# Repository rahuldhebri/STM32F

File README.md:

# STM32F4
* STM32F4 microcontroller board with 10 GPIO pins with terminal connectors, SWD, I2C, USART & USB for DFU.
* Designed in KiCAD all source and manufacturing files included.
* Assembly and Gerber files are in format which JLCPCB uses and all parts used are basic parts so additional cost is not charged for using extended parts.
* Feel free to make any changes and use for your project and also mention suggestions/improvements/issues.

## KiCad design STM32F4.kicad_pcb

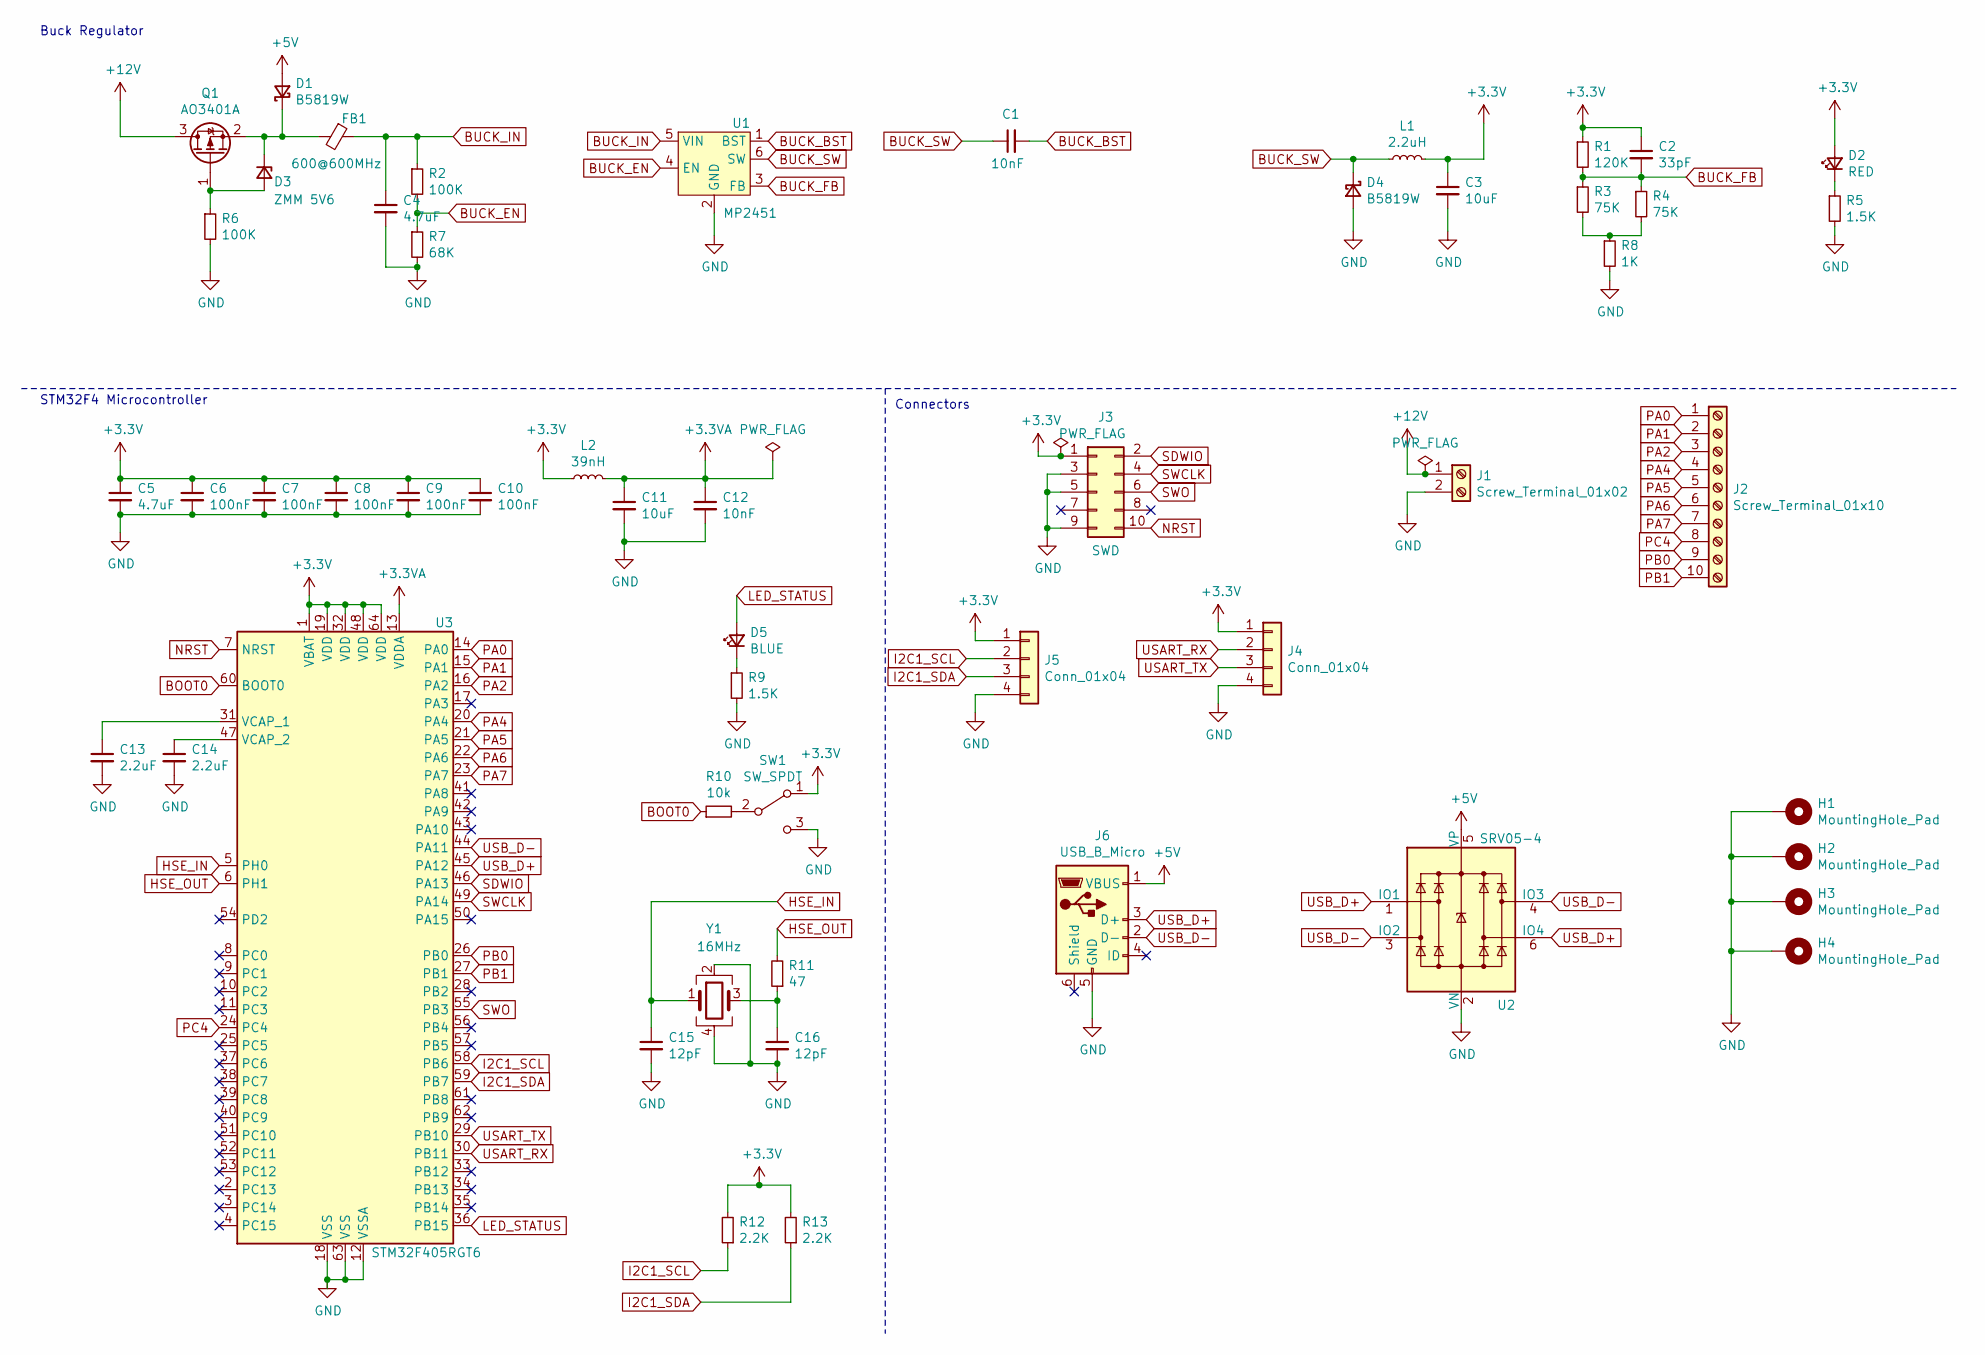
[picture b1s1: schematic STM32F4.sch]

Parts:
C1: 10nF; C_0603_1608Metric; LCSC C57112
C2: 33pF; C_0603_1608Metric; LCSC C1663
C3, C11: 10uF; C_0805_2012Metric; LCSC C15850
C4: 4.7uF; C_0805_2012Metric; LCSC C1779
C5: 4.7uF; C_0402_1005Metric; LCSC C23733
C6, C7, C8, C9, C10: 100nF; C_0402_1005Metric; LCSC C1525
C12: 10nF; C_0402_1005Metric; LCSC C1523
C13, C14: 2.2uF; C_0603_1608Metric; LCSC C23630
C15, C16: 12pF; C_0402_1005Metric; LCSC Part # C1547
D1, D4: B5819W; D_SOD-123; LCSC C8598
D2: RED; LED_0603_1608Metric; LCSC C2286
D3: ZMM 5V6; D_MiniMELF; LCSC Part # C8062
D5: BLUE; LED_0603_1608Metric; LCSC Part # C72041
FB1: 600@600MHz; L_0805_2012Metric; LCSC C1017
H1, H2, H3, H4: MountingHole_Pad; MountingHole_3.2mm_M3_Pad_Via
J1: Screw_Terminal_01x02; TerminalBlock_Phoenix_MKDS-3-2-5.08_1x02_P5.08mm_Horizontal
J2: Screw_Terminal_01x10; TerminalBlock_Phoenix_MKDS-1,5-10_1x10_P5.00mm_Horizontal
J3: SWD; PinHeader_2x05_P1.27mm_Vertical_SMD
J4, J5: Conn_01x04; Molex_SL_171971-0004_1x04_P2.54mm_Vertical
J6: USB_B_Micro; USB_Micro-B_Amphenol_10103594-0001LF_Horizontal
L1: 2.2uH; L_1210_3225Metric; LCSC Part # C1043
L2: 39nH; L_0402_1005Metric; LCSC Part # C25808
Q1: AO3401A; SOT-23; LCSC Part # C15127
R1: 120K; R_0603_1608Metric; LCSC Part # C25808
R2: 100K; R_0603_1608Metric; LCSC Part # C25803
R3, R4: 75K; R_0603_1608Metric; LCSC Part # C23242
R5, R9: 1.5K; R_0603_1608Metric; LCSC C22843
R6: 100K; R_0603_1608Metric; LCSC C25803
R7: 68K; R_0603_1608Metric; LCSC Part # C23231
R8: 1K; R_0603_1608Metric; LCSC Part # C21190
R10: 10k; R_0402_1005Metric; LCSC Part # C25744
R11: 47; R_0603_1608Metric; LCSC Part # C23182
R12, R13: 2.2K; R_0603_1608Metric; LCSC Part # C4190
SW1: SW_SPDT; SW_CuK_OS102011MA1QN1_SPDT_Angled
U1: MP2451; SOT-23-6; LCSC Part # C14123
U2: SRV05-4; SOT-23-6; LCSC Part # C85364
U3: STM32F405RGT6; LQFP-64_10x10mm_P0.5mm; LCSC Part # C15742
Y1: 16MHz; Crystal_SMD_3225-4Pin_3.2x2.5mm; LCSC Part # C13738

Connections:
+3.3VA: C11.1, C12.1, L2.2, U3.13 (VDDA)
+3V3: C2.1, C3.1, C5.1, C6.1, C7.1, C8.1, C9.1, C10.1, D2.2 (A), J3.1, J4.1, J5.1, L1.2, L2.1, R1.1, R12.2, R13.2, SW1.1 (A), U3.1 (VBAT), U3.19 (VDD), U3.32 (VDD), U3.48 (VDD), U3.64 (VDD)
+5V: D1.2 (A), J6.1 (VBUS), U2.5 (VP)
+12V: J1.1, Q1.3 (D)
BOOT0: R10.1, U3.60 (BOOT0)
BUCK_BST: C1.2, U1.1 (BST)
BUCK_EN: R2.2, R7.1, U1.4 (EN)
BUCK_FB: C2.2, R1.2, R3.1, R4.1, U1.3 (FB)
BUCK_IN: C4.1, FB1.1, R2.1, U1.5 (VIN)
BUCK_SW: C1.1, D4.1 (K), L1.1, U1.6 (SW)
GND: C3.2, C4.2, C5.2, C6.2, C7.2, C8.2, C9.2, C10.2, C11.2, C12.2, C13.2, C14.2, C15.2, C16.2, D4.2 (A), H1.1, H2.1, H3.1, H4.1, J1.2, J3.3, J3.5, J3.9, J4.4, J5.4, J6.5 (GND), R5.2, R6.2, R7.2, R8.2, R9.2, SW1.3 (C), U1.2 (GND), U2.2 (VN), U3.12 (VSSA), U3.18 (VSS), U3.63 (VSS), Y1.2, Y1.4
HSE_IN: C15.1, U3.5 (PH0), Y1.1
HSE_OUT: R11.2, U3.6 (PH1)
I2C1_SCL: J5.2, R12.1, U3.58 (PB6)
I2C1_SDA: J5.3, R13.1, U3.59 (PB7)
LED_STATUS: D5.2 (A), U3.36 (PB15)
NRST: J3.10, U3.7 (NRST)
unnamed: C13.1, U3.31 (VCAP_1)
unnamed: C14.1, U3.47 (VCAP_2)
unnamed: C16.1, R11.1, Y1.3
unnamed: D1.1 (K), D3.1 (K), FB1.2, Q1.2 (S)
unnamed: D2.1 (K), R5.1
unnamed: D3.2 (A), Q1.1 (G), R6.1
unnamed: D5.1 (K), R9.1
unnamed: R3.2, R4.2, R8.1
unnamed: R10.2, SW1.2 (B)
PA0: J2.1, U3.14 (PA0)
PA1: J2.2, U3.15 (PA1)
PA2: J2.3, U3.16 (PA2)
PA4: J2.4, U3.20 (PA4)
PA5: J2.5, U3.21 (PA5)
PA6: J2.6, U3.22 (PA6)
PA7: J2.7, U3.23 (PA7)
PB0: J2.9, U3.26 (PB0)
PB1: J2.10, U3.27 (PB1)
PC4: J2.8, U3.24 (PC4)
SDWIO: J3.2, U3.46 (PA13)
SWCLK: J3.4, U3.49 (PA14)
SWO: J3.6, U3.55 (PB3)
USART_RX: J4.2, U3.30 (PB11)
USART_TX: J4.3, U3.29 (PB10)
USB_D+: J6.3 (D+), U2.1 (IO1), U2.6 (IO4), U3.45 (PA12)
USB_D-: J6.2 (D-), U2.3 (IO2), U2.4 (IO3), U3.44 (PA11)

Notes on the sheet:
STM32F4 Microcontroller
Buck Regulator
Connectors

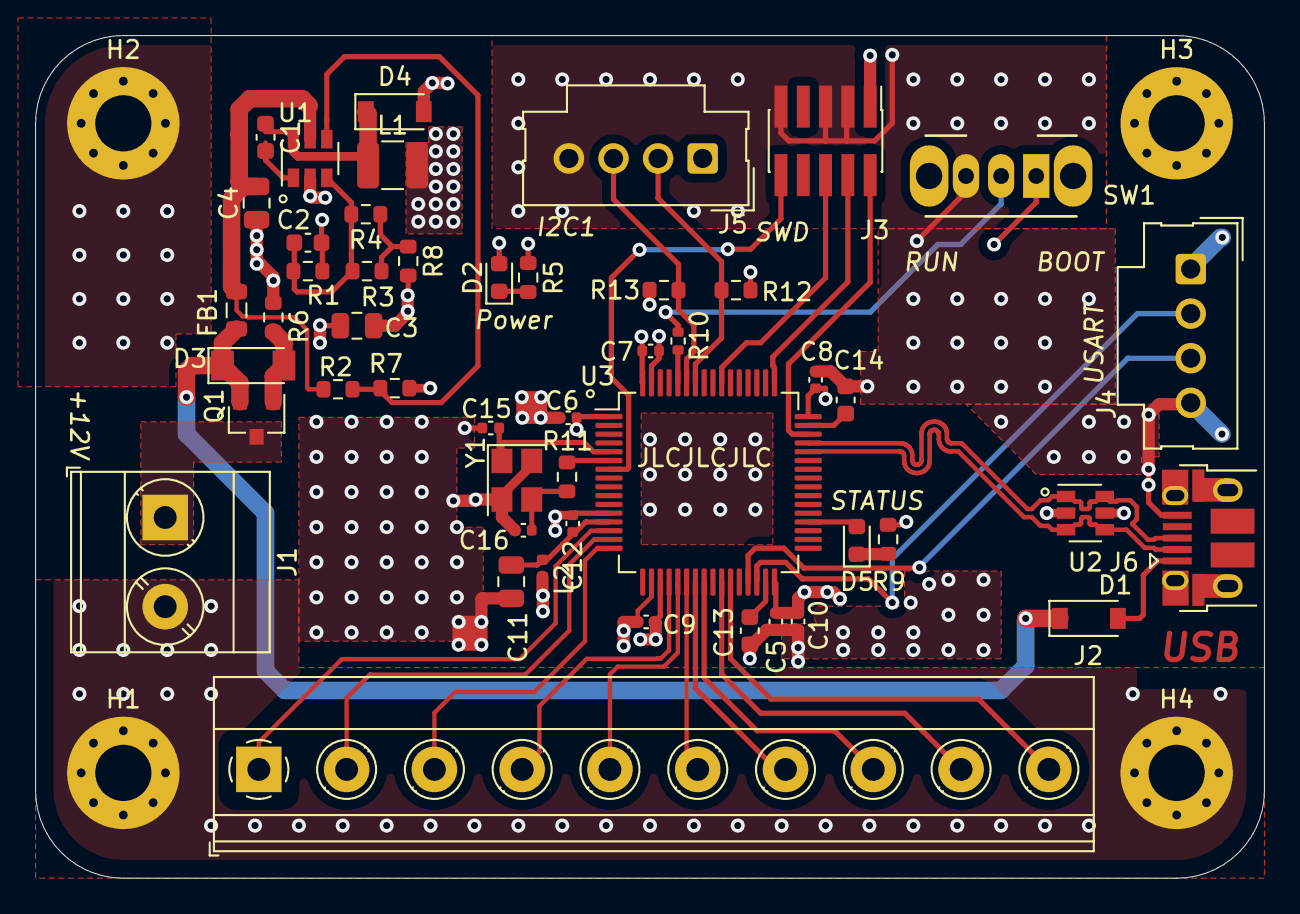
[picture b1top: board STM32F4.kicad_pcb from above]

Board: 4 copper layers, 70.0 x 48.0 mm, 53 parts (0 on the bottom side), 43 nets.

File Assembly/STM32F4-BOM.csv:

Comment,Designator,Footprint,LCSC
"10nF","C1","Capacitor_SMD:C_0603_1608Metric","C57112"
"100nF","C6,C7,C8,C9,C10","Capacitor_SMD:C_0402_1005Metric","C1525"
"10nF","C12","Capacitor_SMD:C_0402_1005Metric","C1523"
"2.2uF","C13,C14","Capacitor_SMD:C_0603_1608Metric","C23630"
"12pF","C15,C16","Capacitor_SMD:C_0402_1005Metric","C1547"
"33pF","C2","Capacitor_SMD:C_0603_1608Metric","C1663"
"10uF","C3,C11","Capacitor_SMD:C_0805_2012Metric","C15850"
"4.7uF","C4","Capacitor_SMD:C_0805_2012Metric","C1779"
"4.7uF","C5","Capacitor_SMD:C_0402_1005Metric","C23733"
"B5819W","D1,D4","Diode_SMD:D_SOD-123","C8598"
"RED","D2","LED_SMD:LED_0603_1608Metric","C2286"
"ZMM 5V6","D3","Diode_SMD:D_MiniMELF","C8062"
"BLUE","D5","LED_SMD:LED_0603_1608Metric","C72041"
"600@600MHz","FB1","Inductor_SMD:L_0805_2012Metric","C1017"
"MountingHole_Pad","H1,H2,H3,H4","MountingHole:MountingHole_3.2mm_M3_Pad_Via",""
"Screw_Terminal_01x02","J1","TerminalBlock_Phoenix:TerminalBlock_Phoenix_MKDS-3-2-5.08_1x02_P5.08mm_Horizontal",""
"Screw_Terminal_01x10","J2","TerminalBlock_Phoenix:TerminalBlock_Phoenix_MKDS-1,5-10_1x10_P5.00mm_Horizontal",""
"SWD","J3","Connector_PinHeader_1.27mm:PinHeader_2x05_P1.27mm_Vertical_SMD",""
"Conn_01x04","J4,J5","Connector_Molex:Molex_SL_171971-0004_1x04_P2.54mm_Vertical",""
"USB_B_Micro","J6","Connector_USB:USB_Micro-B_Amphenol_10103594-0001LF_Horizontal",""
"2.2uH","L1","Inductor_SMD:L_1210_3225Metric","C1043"
"39nH","L2","Inductor_SMD:L_0402_1005Metric","C25808"
"AO3401A","Q1","Package_TO_SOT_SMD:SOT-23","C15127"
"120K","R1","Resistor_SMD:R_0603_1608Metric","C25808"
"10k","R10","Resistor_SMD:R_0402_1005Metric","C25744"
"47","R11","Resistor_SMD:R_0603_1608Metric","C23182"
"2.2K","R12,R13","Resistor_SMD:R_0603_1608Metric","C4190"
"100K","R2,R6","Resistor_SMD:R_0603_1608Metric",""
"75K","R3,R4","Resistor_SMD:R_0603_1608Metric","C23242"
"1.5K","R5,R9","Resistor_SMD:R_0603_1608Metric","C22843"
"68K","R7","Resistor_SMD:R_0603_1608Metric","C23231"
"1K","R8","Resistor_SMD:R_0603_1608Metric","C21190"
"SW_SPDT","SW1","Button_Switch_THT:SW_CuK_OS102011MA1QN1_SPDT_Angled",""
"MP2451","U1","Package_TO_SOT_SMD:SOT-23-6","C14123"
"SRV05-4","U2","Package_TO_SOT_SMD:SOT-23-6","C85364"
"STM32F405RGT6","U3","Package_QFP:LQFP-64_10x10mm_P0.5mm","C15742"
"16MHz","Y1","Crystal:Crystal_SMD_3225-4Pin_3.2x2.5mm","C13738"

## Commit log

2021-03-08 Second commit
2021-03-08 README.md
2021-03-08 Third Commit
2021-03-08 Fourth Commit
